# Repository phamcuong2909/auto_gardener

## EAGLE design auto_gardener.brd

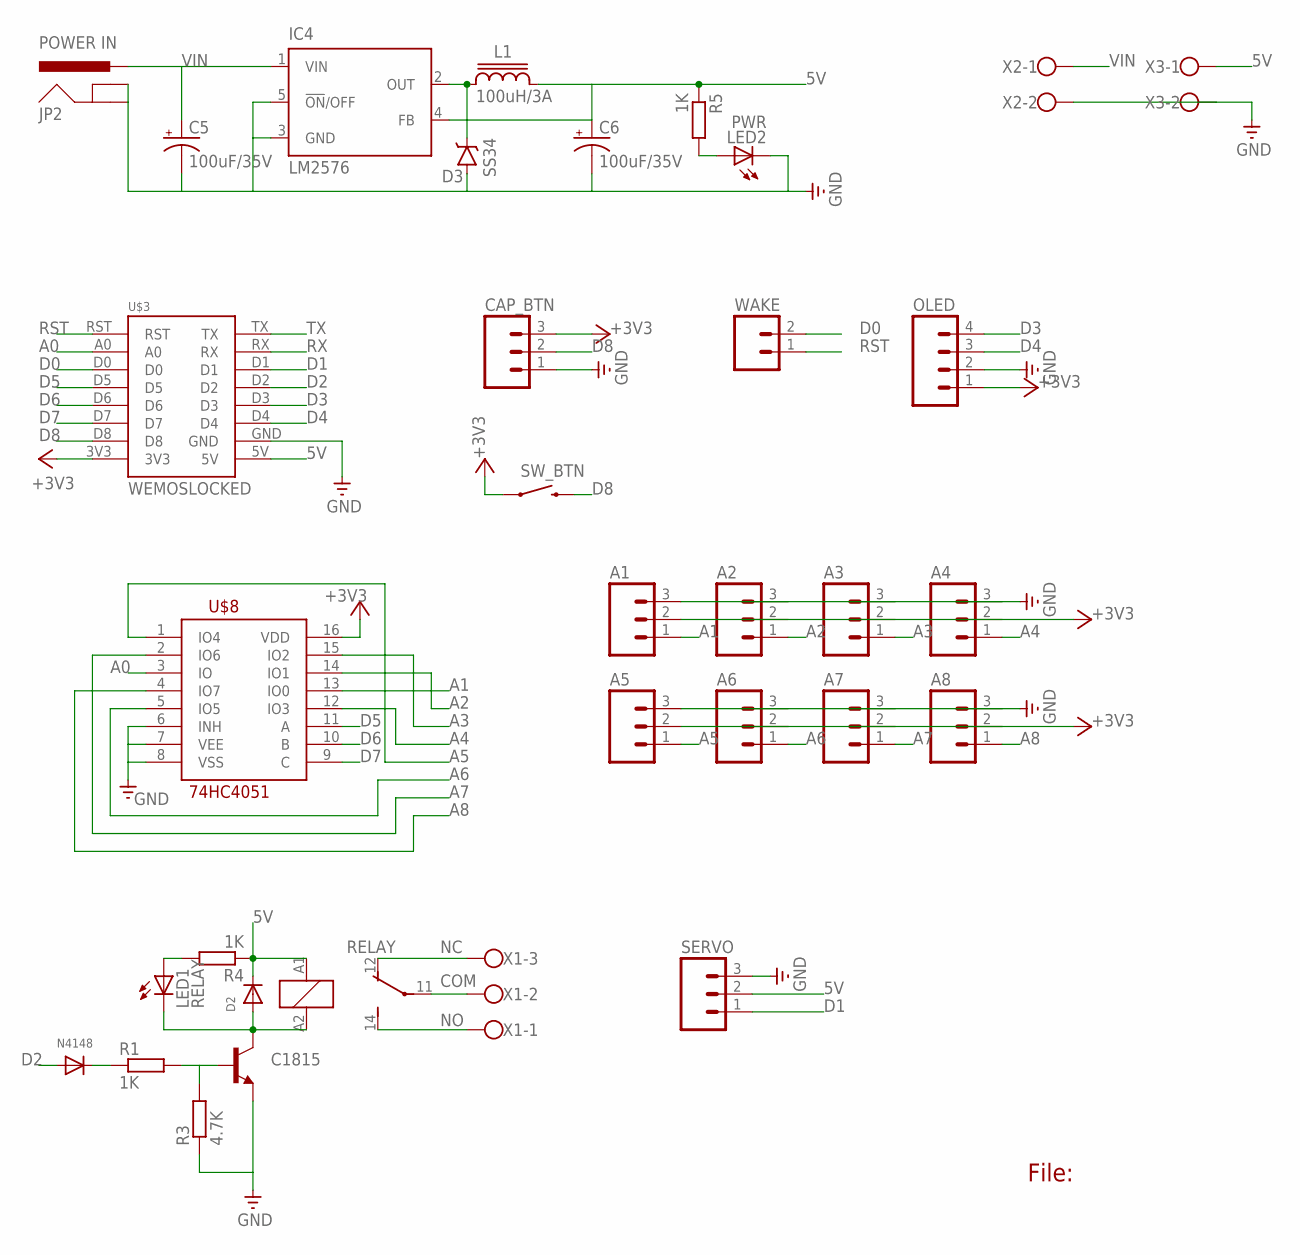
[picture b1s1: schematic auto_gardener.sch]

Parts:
A1, A2, A3, A4, A5, A6, A7, A8: M03PTH; 1X03
C5, C6: 100uF/35V; PANASONIC_D
C1815: TRANSISTOR_NPNSOT23-3; SOT23-3
CAP_BTN: M03PTH; 1X03
D2: DIODESMA; SMADIODE
D3: SS34; SMA-DIODE
IC4: LM2576; TO263-5
JP2: POWER IN; POWER_JACK_PTH
L1: 100uH/3A; CDRH127/LD
LED1: RELAY; LED3MM
LED2: PWR; LED3MM
N4148: DIODESOD-123; SOD-123
OLED: M04PTH; 1X04
R1, R4, R5: 1K; R0805
R3: 4.7K; R0805
RELAY: ZNS5106; ZN5
SERVO: M03PTH; 1X03
SW_BTN: SWITCH-MOMENTARY-212MM; TACTILE-PTH-12MM
U$3: WEMOSLOCKED; WEMOS_LOCKED
U$8: 74HC4051
WAKE: M02PTH; 1X02
X1: W237-103
X2, X3: W237-102

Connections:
5V: C6.+, D2.C, IC4.4 (FB), L1.2, R4.1, R5.1, RELAY.A1 (1), SERVO.2, U$3.5V, X3.1
+3V3: A1.2, A2.2, A3.2, A4.2, A5.2, A6.2, A7.2, A8.2, CAP_BTN.3, OLED.1, SW_BTN.1, U$3.3V3, U$8.16 (VDD)
A0: U$3.A0, U$8.3 (IO)
A1: A1.1, U$8.13 (IO0)
A2: A2.1, U$8.14 (IO1)
A3: A3.1, U$8.15 (IO2)
A4: A4.1, U$8.12 (IO3)
A5: A5.1, U$8.1 (IO4)
A6: A6.1, U$8.5 (IO5)
A7: A7.1, U$8.2 (IO6)
A8: A8.1, U$8.4 (IO7)
COM: RELAY.11, X1.2
D0: U$3.D0, WAKE.2
D1: SERVO.1, U$3.D1
D2: N4148.A, U$3.D2
D3: OLED.4, U$3.D3
D4: OLED.3, U$3.D4
D5: U$3.D5, U$8.11 (A)
D6: U$3.D6, U$8.10 (B)
D7: U$3.D7, U$8.9 (C)
D8: CAP_BTN.2, SW_BTN.3 (2), U$3.D8
GND: A1.3, A2.3, A3.3, A4.3, A5.3, A6.3, A7.3, A8.3, C5.-, C6.-, C1815.2 (E), CAP_BTN.1, D3.A, IC4.3 (GND), IC4.5 (!ON!/OFF), JP2.GND, JP2.GNDBREAK, LED2.K (C), OLED.2, R3.1, SERVO.3, U$3.GND, U$8.6 (INH), U$8.7 (VEE), U$8.8 (VSS), X2.2, X3.2
unnamed: C1815.3 (C), D2.A, LED1.K (C), RELAY.A2 (2)
unnamed: N4148.C, R1.1
unnamed: LED1.A, R4.2
unnamed: LED2.A, R5.2
unnamed: C1815.1 (B), R1.2, R3.2
unnamed: D3.C, IC4.2 (OUT), L1.1
NC: RELAY.12 (O), X1.3
NO: RELAY.14 (S), X1.1
RST: U$3.RST, WAKE.1
RX: U$3.RX
TX: U$3.TX
VIN: C5.+, IC4.1 (VIN), JP2.PWR, X2.1

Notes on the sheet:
File:

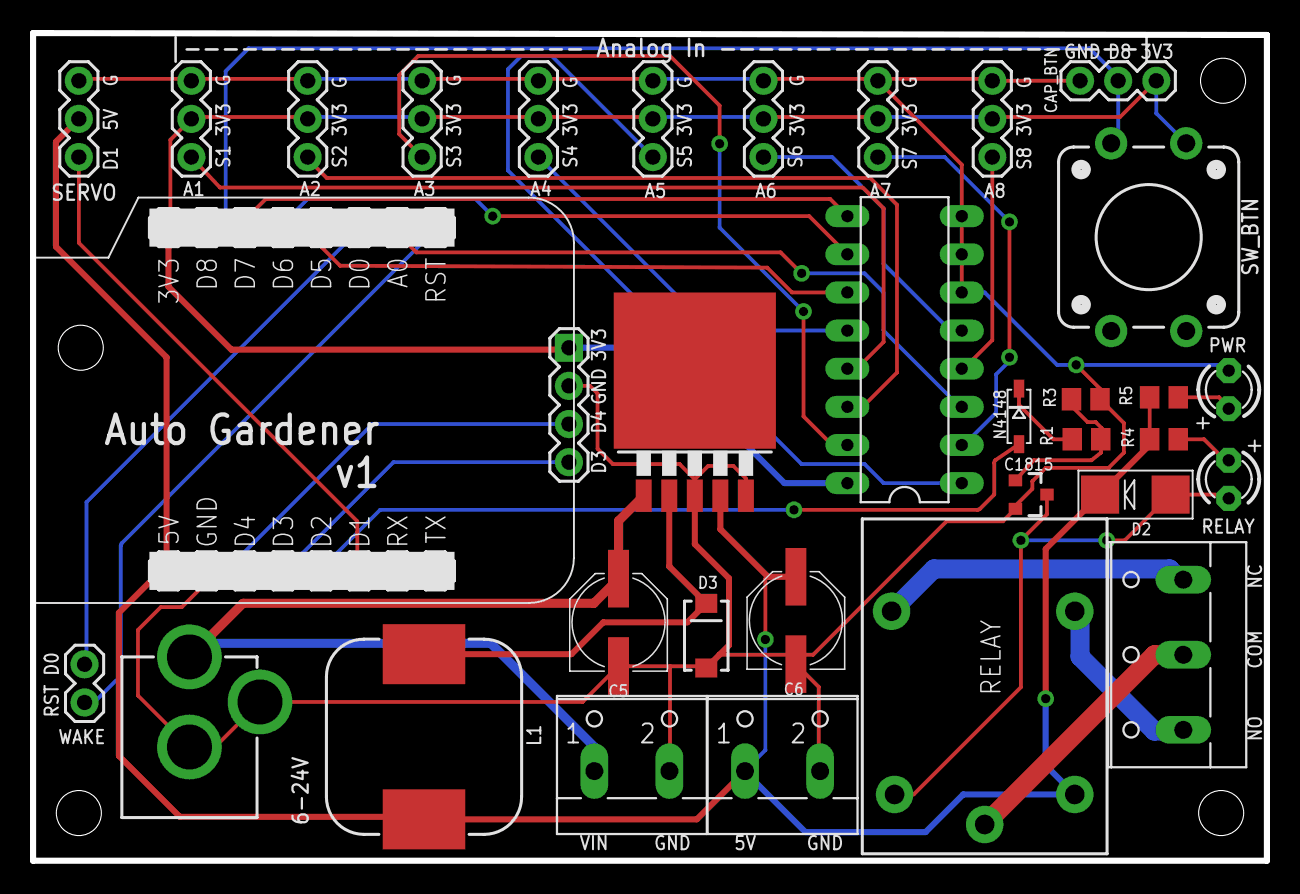
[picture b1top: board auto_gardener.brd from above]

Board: 2 copper layers, 82.2 x 55.1 mm, 38 parts (0 on the bottom side), 32 nets.

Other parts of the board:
U$2, U$5, U$6, U$7: KFH-M3

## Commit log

2016-10-02 Add initial design and sample code
2016-10-02 Update design to add one more AMS1117 for servo
2016-11-10 Update sample code

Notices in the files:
parts and their libraries:
SparkFun-Connectors: Licensing: Creative Commons ShareAlike 4.0 International - https://creativecommons.org/licenses/by-sa/4.0
penn-engineering: Copyright (C) 2010, Bob Starr
inductor-sumida: Copyright (C) 2008, Bob Starr
